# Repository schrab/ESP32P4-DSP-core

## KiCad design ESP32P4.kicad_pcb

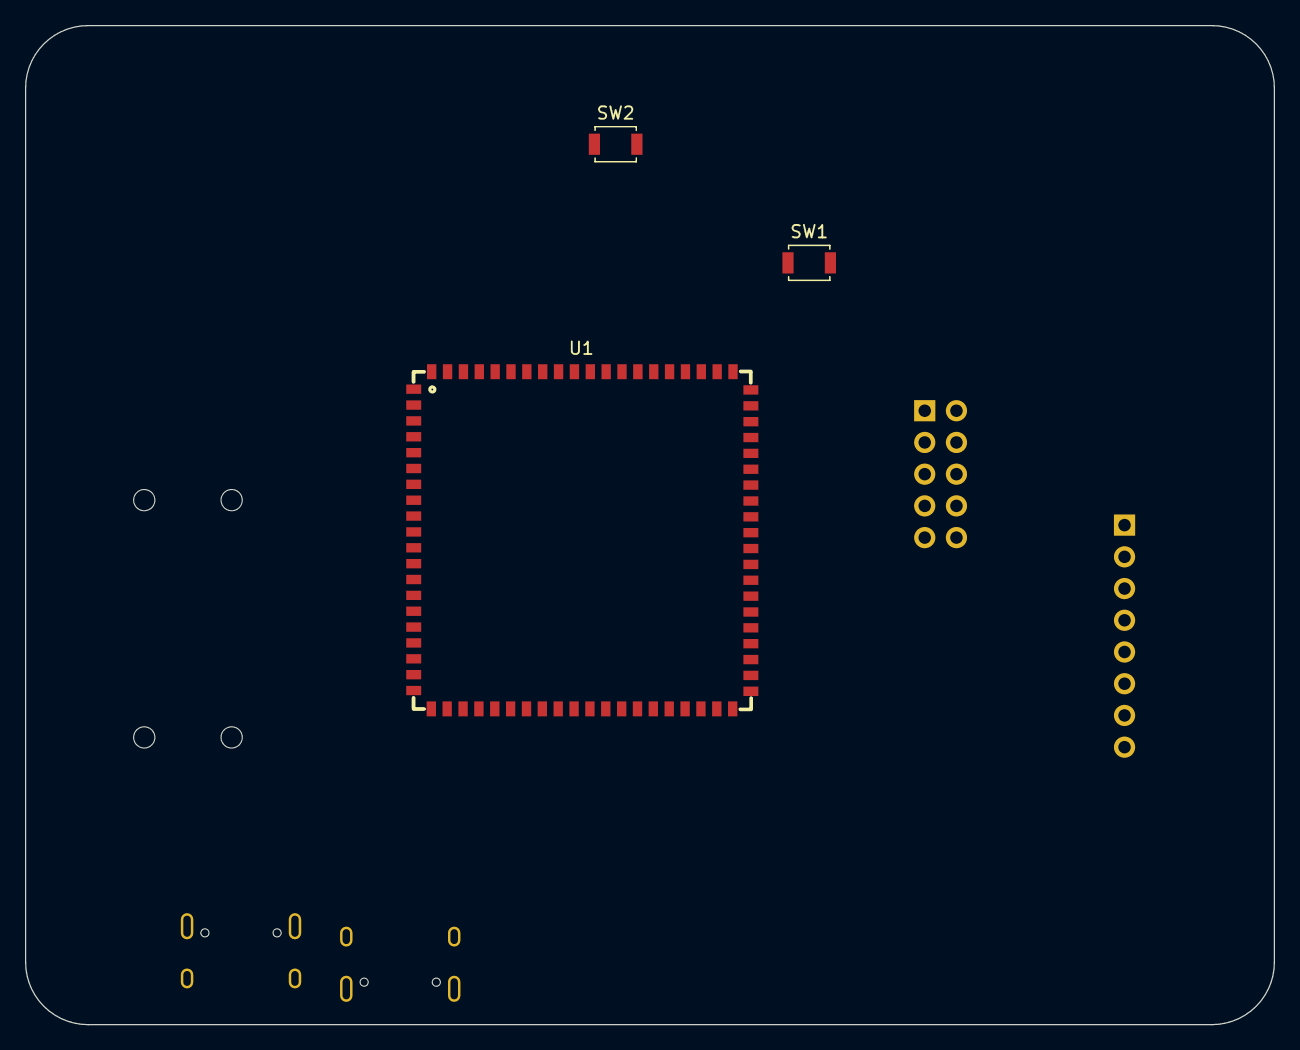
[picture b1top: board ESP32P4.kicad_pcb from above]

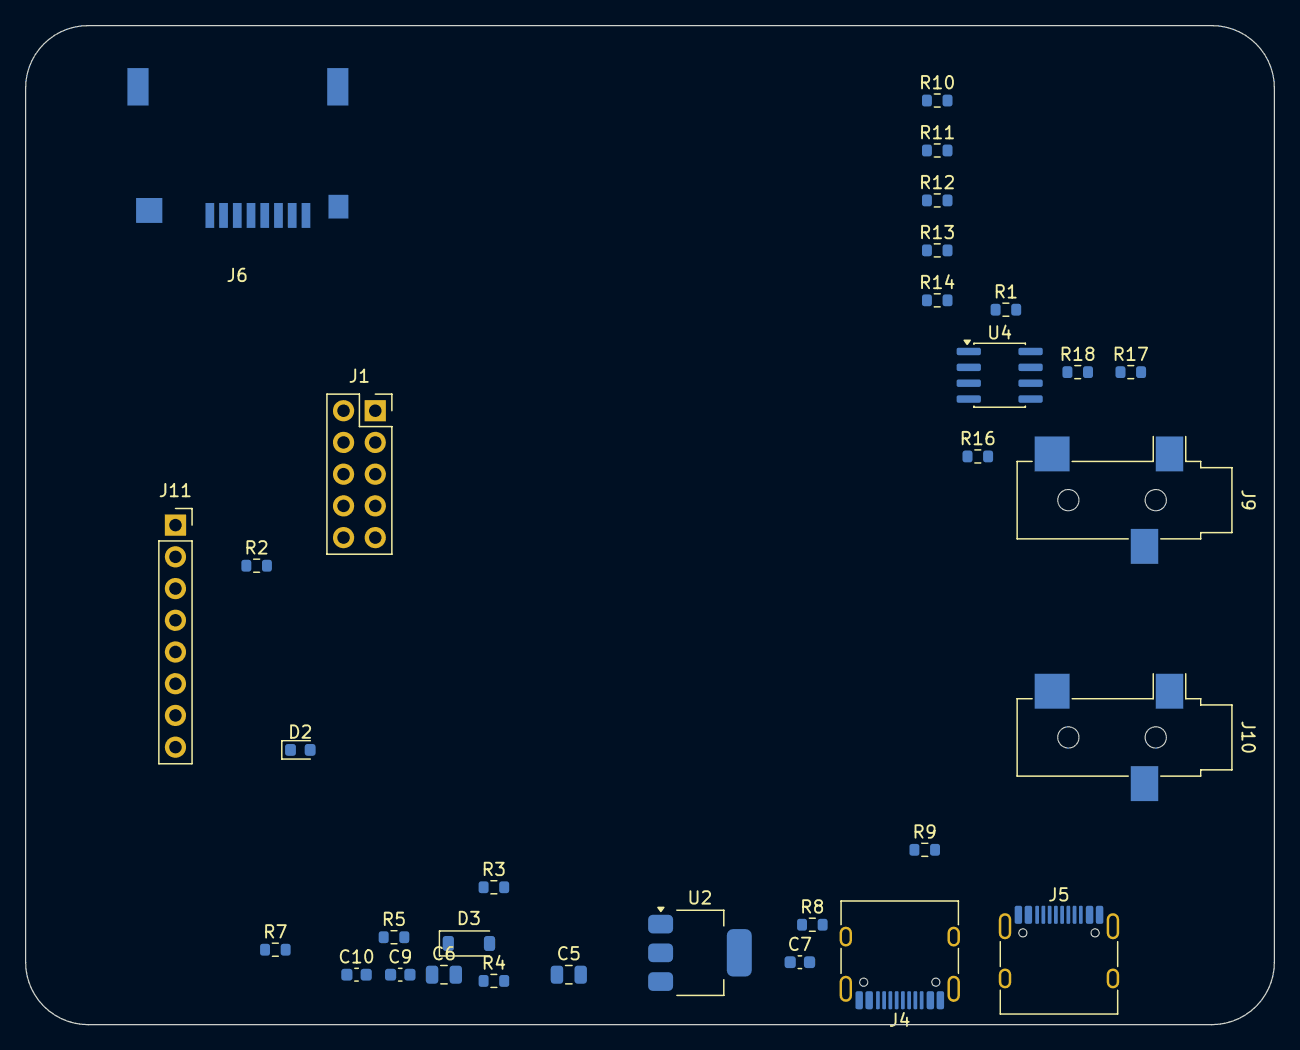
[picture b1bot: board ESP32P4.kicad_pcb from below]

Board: 2 copper layers, 100.0 x 80.0 mm, 35 parts (32 on the bottom side), 40 nets, no tracks yet.

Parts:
C5: 10u; C_0805_2012Metric
C6: 22u; C_0805_2012Metric
C7: 1u; C_0603_1608Metric
C9, C10: 100n; C_0603_1608Metric
D2: PWR; LED_0603_1608Metric
D3: 1N4148W; D_SOD-123
J1: WM8978_BRK; PinSocket_2x05_P2.54mm_Vertical
J4: USB-C_DEV; USB_C_Receptacle_HRO_TYPE-C-31-M-12
J5: USB-C_HOST; USB_C_Receptacle_HRO_TYPE-C-31-M-12
J6: microSD; TFP09-2-12B
J9: MIDI_OUT; Jack_3.5mm_CUI_SJ-3523-SMT_Horizontal
J10: MIDI_IN; Jack_3.5mm_CUI_SJ-3523-SMT_Horizontal
J11: UI_BOARD; PinSocket_1x08_P2.54mm_Vertical
R1, R2, R18: 4.7K; R_0603_1608Metric
R3, R4, R5: 10K; R_0603_1608Metric
R7, R8, R9: 5.1K; R_0603_1608Metric
R10, R11, R12, R13: 47K; R_0603_1608Metric
R14: 0R; R_0603_1608Metric
R16, R17: 33R; R_0603_1608Metric
SW1: BOOT; SW_SPST_B3U-1000P
SW2: RESET; SW_SPST_B3U-1000P
U1: ESP32P4_QFN104; JC-ESP32P4-M3_V0.2
U2: LM1117MP-3.3; SOT-223-3_TabPin2
U4: 6N137; SOIC-8_3.9x4.9mm_P1.27mm

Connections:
+3V3: C6.1, C9.1, C10.1, J1.8, J11.2, R1.2, R2.2, R3.2, R4.2, R5.2, R7.1, R17.1, R18.2, U1.77 (ESP_3V3), U1.78 (ESP_3V3), U2.2, U4.7, U4.8
+3V3_LED: D2.2, R7.2
+5V: C5.1, J5.A4, J5.A9, J5.B4, J5.B9, U2.3
BOOT: R3.1, SW1.1, U1.54 (GPIO35)
CC1: J4.A5, R8.1
CC2: J4.B5, R9.1
GND: C5.2, C6.2, C7.2, C9.2, C10.2, D2.1, J1.7, J4.A1, J4.A12, J4.B1, J4.B12, J4.SH, J5.A1, J5.A12, J5.B1, J5.B12, J5.SH, J6.6, J6.SH, J9.S, J10.S, J11.1, R8.2, R9.2, SW1.2, SW2.2, U1.1 (GND), U1.3 (GND), U1.7 (GND), U1.25 (GND), U1.32 (GND), U1.41 (GND), U1.44 (GND), U1.79 (GND), U1.80 (GND), U2.1, U4.5
GPIO36: R5.1, U1.55 (GPIO36)
I2C_SCL: J1.9, R2.1, U1.12 (GPIO8)
I2C_SDA: J1.10, R1.1, U1.11 (GPIO7)
I2S_BCLK: J1.3, U1.67 (GPIO47)
I2S_DIN: J1.4, U1.6 (GPIO3)
I2S_DOUT: J1.1, U1.8 (GPIO4)
I2S_MCLK: J1.2, U1.66 (GPIO46)
I2S_WS: J1.6, U1.9 (GPIO5)
MIDI_IN_RING: D3.1, J10.R, U4.2
MIDI_IN_TIP: D3.2, J10.T, U4.3
MIDI_RING: J9.R, R17.2
MIDI_RX: R18.1, U4.6
MIDI_TIP: J9.T, R16.2
NRST: C7.1, R4.1, SW2.1, U1.75 (CHIP_PU)
PICO_RESET: J11.8, U1.65 (GPIO45)
SD_CLK: J6.5, U1.64 (GPIO44)
SD_CMD: J6.3, R10.1, U1.63 (GPIO43)
SD_D0: J6.7, R11.1, U1.59 (GPIO39)
SD_D1: J6.8, R12.1, U1.60 (GPIO40)
SD_D2: J6.1, R13.1, U1.61 (GPIO41)
SD_D3: J6.2, U1.62 (GPIO42)
SD_PWR: J6.4, R10.2, R11.2, R12.2, R13.2, R14.1
SD_PWR_LDO: R14.2, U1.58 (ESP_LDO_VO4)
SPI_CS: J11.6, U1.4 (GPIO1)
SPI_HS: J11.7, U1.5 (GPIO2)
SPI_MISO: J11.4, U1.52 (GPIO33)
SPI_MOSI: J11.3, U1.51 (GPIO32)
SPI_SCLK: J11.5, U1.21 (GPIO20)
USB5V: J4.A4, J4.A9, J4.B4, J4.B9
USBH_DM: J5.A7, J5.B7, U1.42 (USB1_P1_N)
USBH_DP: J5.A6, J5.B6, U1.43 (USB1_P1_P)
USB_DM: J4.A7, J4.B7, U1.39 (ESP_USB_N)
USB_DP: J4.A6, J4.B6, U1.40 (ESP_USB_P)
